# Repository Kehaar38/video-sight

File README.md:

# VIDEO SIGHT

VIDEO SIGHT is a compact digital sight prototype built around Seeed Studio XIAO ESP32-S3 Sense.

The project goal is a low-latency, approximately 1x-feeling video sight with camera input, LCD display, IMU-assisted attitude information, and a lightweight ballistic overlay for airsoft use.

## Current hardware direction

- Main MCU: Seeed Studio XIAO ESP32-S3 Sense
- Camera: XIAO ESP32-S3 Sense camera module
- Display: Waveshare 1.83 inch LCD Rev2 / ST7789P / 240x284
- IMU: BNO055 module
- UI sub-MCU: ATtiny1616
- Battery: protected 18650 cell
- microSD CS: GPIO21 on XIAO ESP32-S3 Sense
- Peripheral power switch: TPS22919, controlled by D6/GPIO43
- Reverse polarity protection: AO3401A P-MOSFET

## Repository layout

```text
docs/
  hardware/
    parts_and_pinout.md
    power/
    reviews/
hardware/
  kicad/
firmware/
  esp32s3/
  attiny1616/
```

## Status

Early hardware design. The current focus is the power path and first test PCB.

See:

- `docs/hardware/parts_and_pinout.md`
- `docs/hardware/power/power_bom.md`
- `docs/hardware/power/power_design_notes.md`
- `docs/hardware/reviews/2026-05-20_power_schematic_review.md`

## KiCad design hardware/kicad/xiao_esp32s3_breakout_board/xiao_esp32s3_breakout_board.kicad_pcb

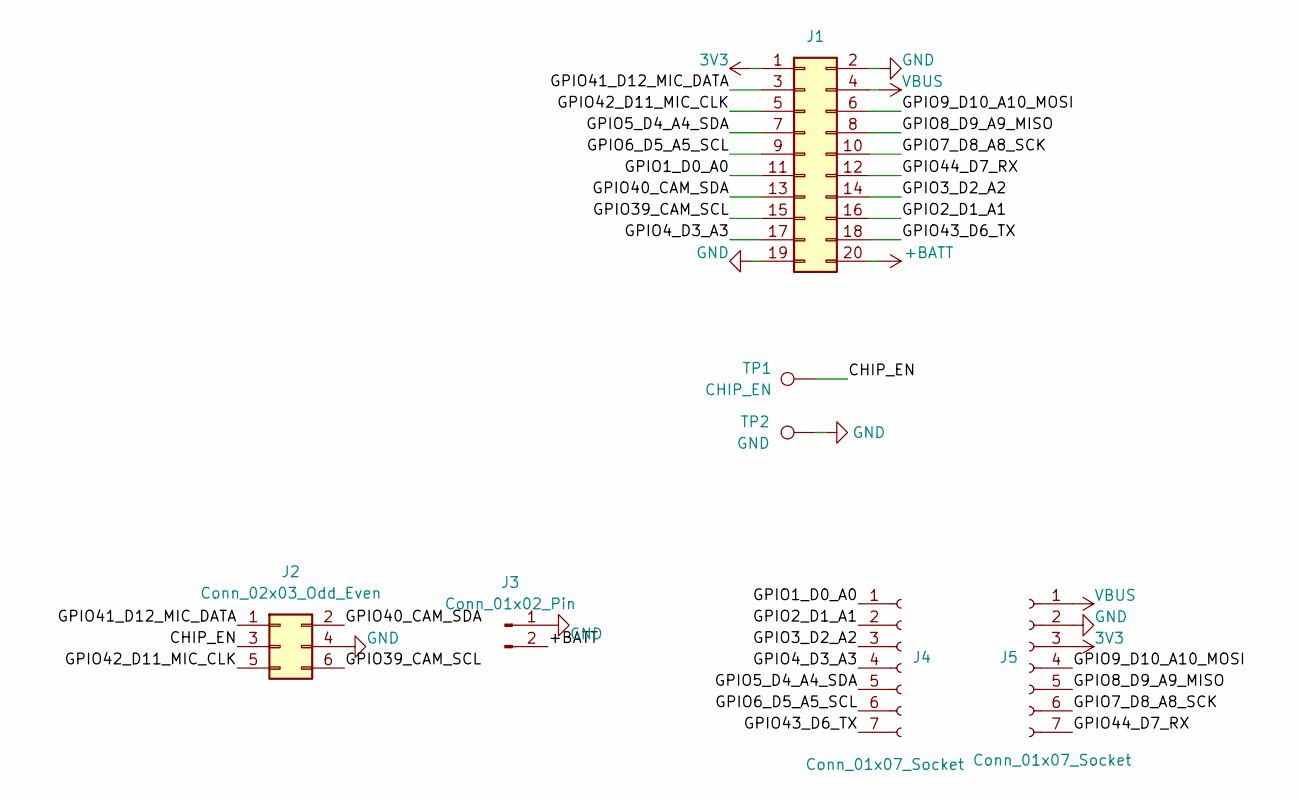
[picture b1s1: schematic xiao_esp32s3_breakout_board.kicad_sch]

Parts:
J1: XIAO_BREAKOUT_BOARD; IDC-Header_2x10_P2.54mm_Vertical
J2: Conn_02x03_Odd_Even; PinHeader_2x03_P2.54mm_Vertical
J3: Conn_01x02_Pin; PinHeader_1x02_P2.00mm_Vertical
J4, J5: Conn_01x07_Socket; PinSocket_1x07_P2.54mm_Vertical
TP1: CHIP_EN; TestPoint_THTPad_D1.5mm_Drill0.7mm
TP2: GND; TestPoint_THTPad_D1.5mm_Drill0.7mm

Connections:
3V3: J1.1, J5.3
+BATT: J1.20, J3.2
/CHIP_EN: J2.3, TP1.1
/GPIO1_D0_A0: J1.11, J4.1
/GPIO2_D1_A1: J1.16, J4.2
/GPIO3_D2_A2: J1.14, J4.3
/GPIO4_D3_A3: J1.17, J4.4
/GPIO5_D4_A4_SDA: J1.7, J4.5
/GPIO6_D5_A5_SCL: J1.9, J4.6
/GPIO7_D8_A8_SCK: J1.10, J5.6
/GPIO8_D9_A9_MISO: J1.8, J5.5
/GPIO9_D10_A10_MOSI: J1.6, J5.4
/GPIO39_CAM_SCL: J1.15, J2.6
/GPIO40_CAM_SDA: J1.13, J2.2
/GPIO41_D12_MIC_DATA: J1.3, J2.1
/GPIO42_D11_MIC_CLK: J1.5, J2.5
/GPIO43_D6_TX: J1.18, J4.7
/GPIO44_D7_RX: J1.12, J5.7
GND: J1.2, J1.19, J2.4, J3.1, J5.2, TP2.1
VBUS: J1.4, J5.1

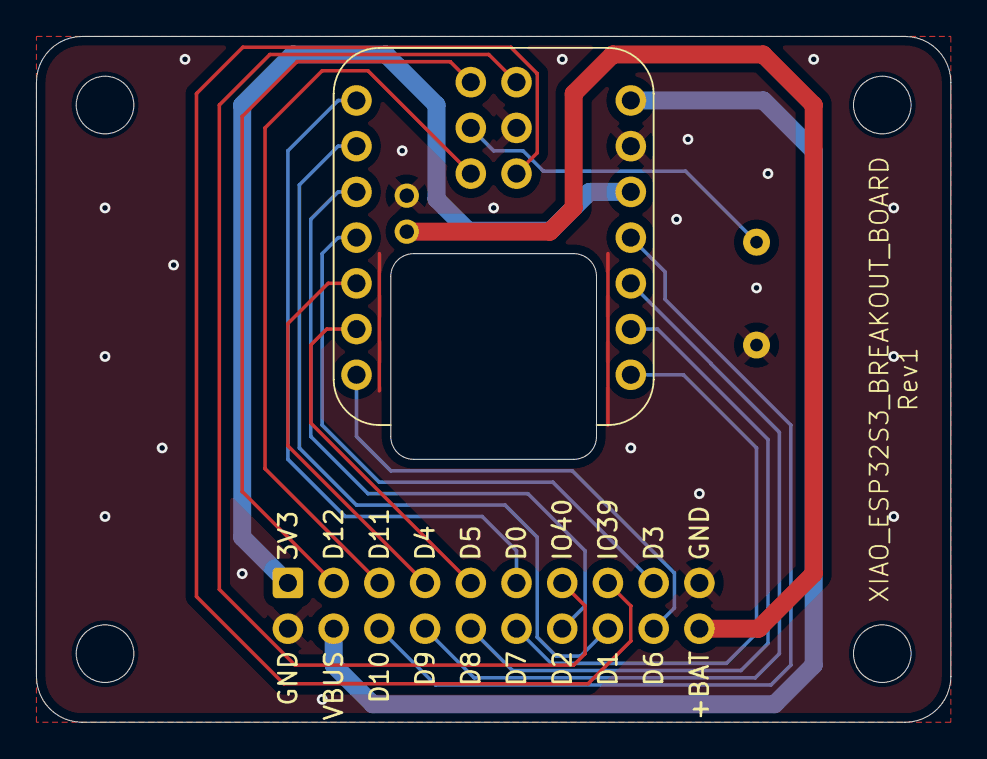
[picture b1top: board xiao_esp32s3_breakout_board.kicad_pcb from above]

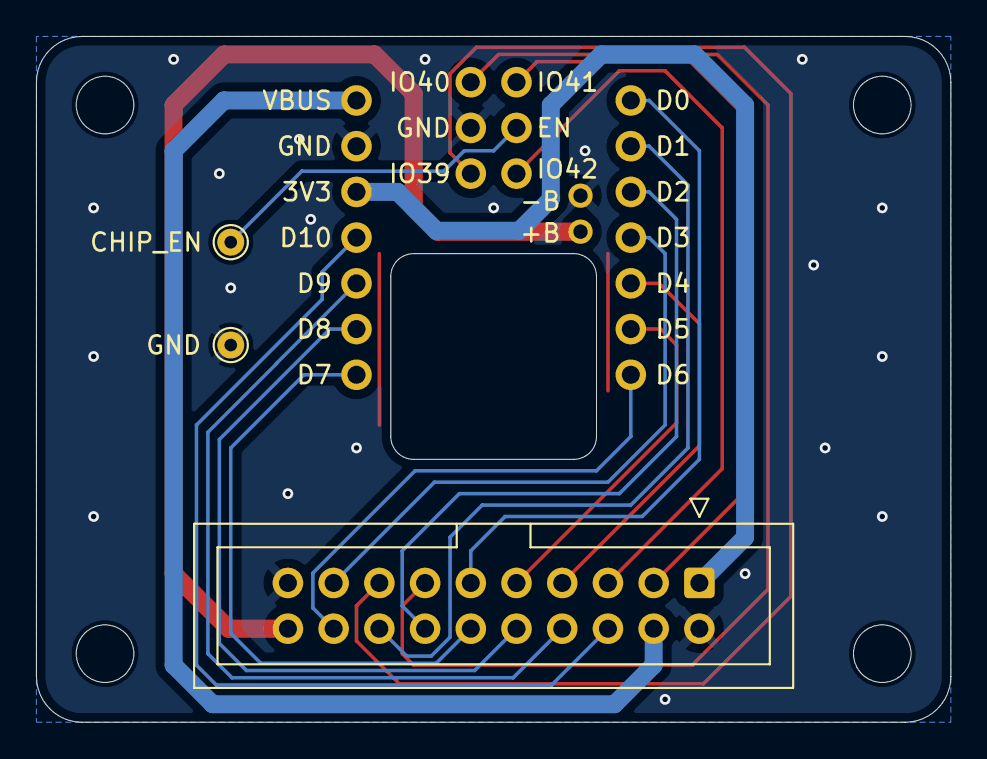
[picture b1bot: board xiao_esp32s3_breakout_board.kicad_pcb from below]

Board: 2 copper layers, 50.8 x 38.1 mm, 7 parts (3 on the bottom side), 20 nets.

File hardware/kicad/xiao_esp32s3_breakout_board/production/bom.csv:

Designator,Footprint,Quantity,Value,LCSC Part #
J1,IDC-Header_2x10_P2.54mm_Vertical,1,XIAO_BREAKOUT_BOARD,
J2,PinHeader_2x03_P2.54mm_Vertical,1,Conn_02x03_Odd_Even,
J3,PinHeader_1x02_P2.00mm_Vertical,1,Conn_01x02_Pin,
"J4, J5",PinSocket_1x07_P2.54mm_Vertical,2,Conn_01x07_Socket,
TP1,TestPoint_THTPad_D1.5mm_Drill0.7mm,1,CHIP_EN,
TP2,TestPoint_THTPad_D1.5mm_Drill0.7mm,1,GND,

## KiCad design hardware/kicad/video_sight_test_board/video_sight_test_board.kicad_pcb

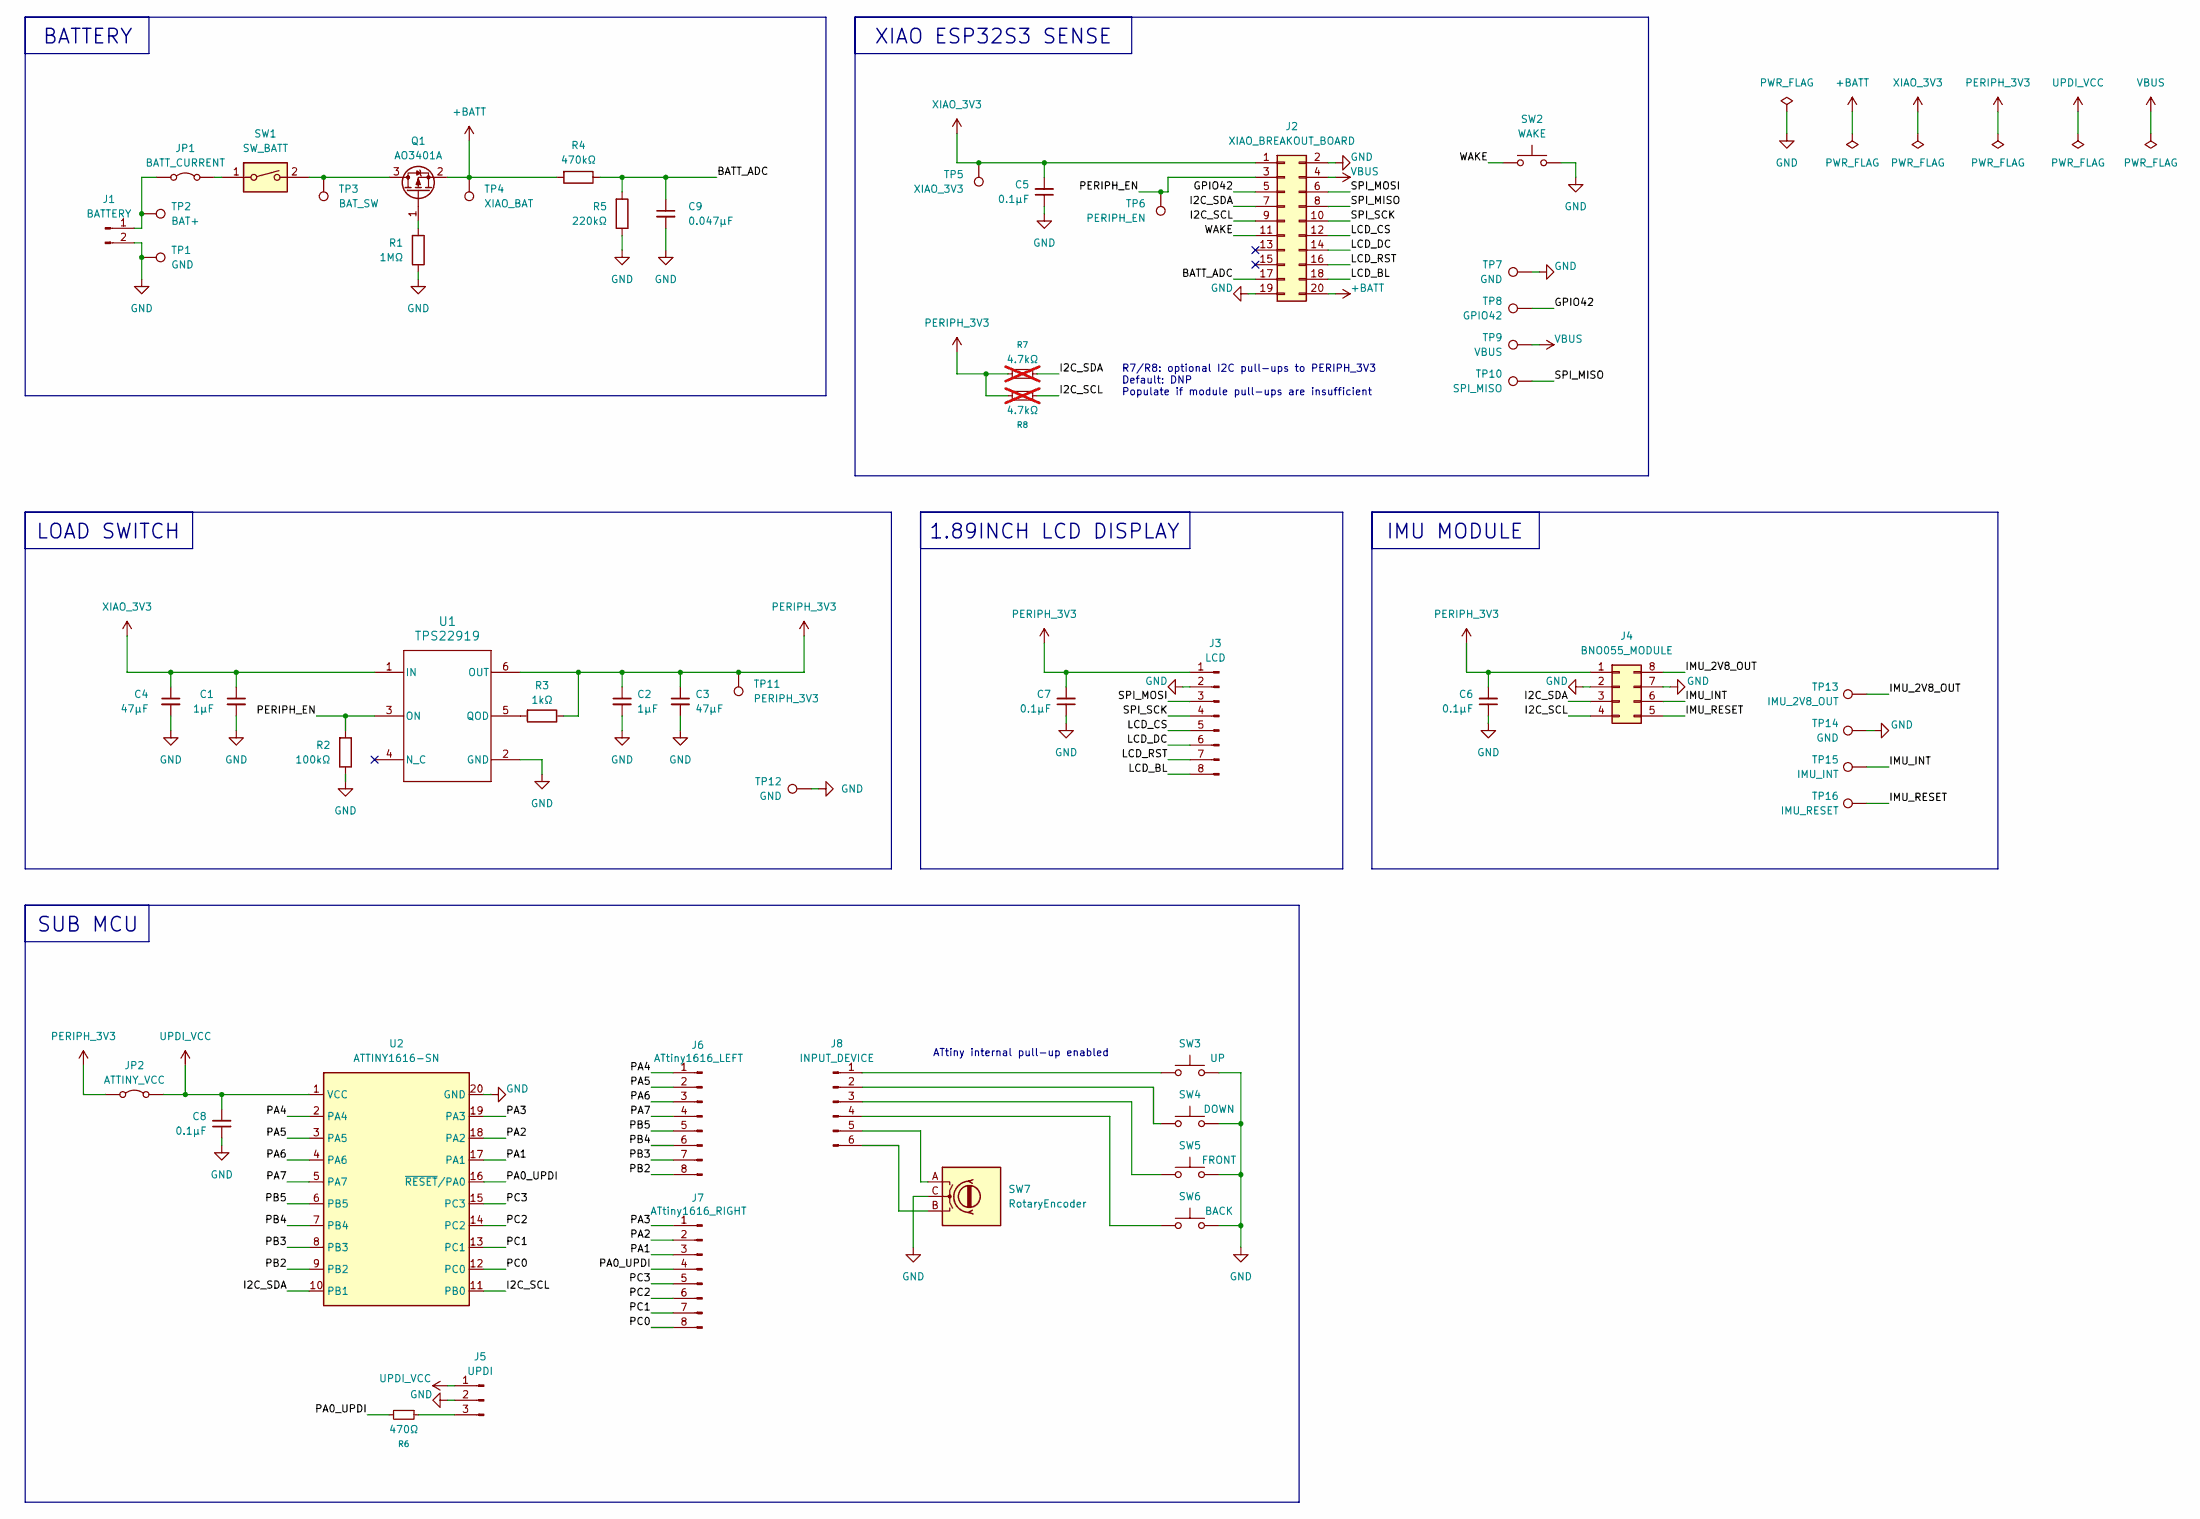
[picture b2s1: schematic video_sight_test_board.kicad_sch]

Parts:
C1, C2: 1μF; C_0805_2012Metric_Pad1.18x1.45mm_HandSolder
C3, C4: 47μF; CAP_FN_B_PAN
C5, C6, C7, C8: 0.1μF; C_0805_2012Metric_Pad1.18x1.45mm_HandSolder
C9: 0.047μF; C_0805_2012Metric_Pad1.18x1.45mm_HandSolder
J1: BATTERY; JST_XH_B2B-XH-A_1x02_P2.50mm_Vertical
J2: XIAO_BREAKOUT_BOARD; IDC-Header_2x10_P2.54mm_Vertical
J3: LCD; PinHeader_1x08_P2.54mm_Vertical
J4: BNO055_MODULE; DIP-8_W7.62mm_Socket
J5: UPDI; PinHeader_1x03_P2.54mm_Vertical
J6: ATtiny1616_LEFT; PinHeader_1x08_P2.54mm_Vertical
J7: ATtiny1616_RIGHT; PinHeader_1x08_P2.54mm_Vertical
J8: INPUT_DEVICE; PinHeader_1x06_P2.54mm_Vertical
JP1: BATT_CURRENT; PinHeader_1x02_P2.54mm_Vertical
JP2: ATTINY_VCC; PinHeader_1x02_P2.54mm_Vertical
Q1: AO3401A; SOT-23
R1: 1MΩ; R_0805_2012Metric_Pad1.20x1.40mm_HandSolder
R2: 100kΩ; R_0805_2012Metric_Pad1.20x1.40mm_HandSolder
R3: 1kΩ; R_0805_2012Metric_Pad1.20x1.40mm_HandSolder
R4: 470kΩ; R_0805_2012Metric_Pad1.20x1.40mm_HandSolder
R5: 220kΩ; R_0805_2012Metric_Pad1.20x1.40mm_HandSolder
R6: 470Ω; R_0805_2012Metric_Pad1.20x1.40mm_HandSolder
R7, R8: 4.7kΩ; R_0805_2012Metric_Pad1.20x1.40mm_HandSolder; not fitted
SW1: SW_BATT; SW_DIP_SPSTx01_Slide_9.78x4.72mm_W7.62mm_P2.54mm
SW2: WAKE; SW_PUSH_6mm
SW3: UP; SW_PUSH_6mm
SW4: DOWN; SW_PUSH_6mm
SW5: FRONT; SW_PUSH_6mm
SW6: BACK; SW_PUSH_6mm
SW7: RotaryEncoder; RotaryEncoder_Alps_EC12E_Vertical_H20mm
TP1, TP7, TP12, TP14: GND; TestPoint_THTPad_D1.5mm_Drill0.7mm
TP2: BAT+; TestPoint_THTPad_D1.5mm_Drill0.7mm
TP3: BAT_SW; TestPoint_THTPad_D1.5mm_Drill0.7mm
TP4: XIAO_BAT; TestPoint_THTPad_D1.5mm_Drill0.7mm
TP5: XIAO_3V3; TestPoint_THTPad_D1.5mm_Drill0.7mm
TP6: PERIPH_EN; TestPoint_THTPad_D1.5mm_Drill0.7mm
TP8: GPIO42; TestPoint_THTPad_D1.5mm_Drill0.7mm
TP9: VBUS; TestPoint_THTPad_D1.5mm_Drill0.7mm
TP10: SPI_MISO; TestPoint_THTPad_D1.5mm_Drill0.7mm
TP11: PERIPH_3V3; TestPoint_THTPad_D1.5mm_Drill0.7mm
TP13: IMU_2V8_OUT; TestPoint_THTPad_D1.5mm_Drill0.7mm
TP15: IMU_INT; TestPoint_THTPad_D1.5mm_Drill0.7mm
TP16: IMU_RESET; TestPoint_THTPad_D1.5mm_Drill0.7mm
U1: TPS22919; DCK0006A_L
U2: ATTINY1616-SN; SOIC-20W_7.5x12.8mm_P1.27mm

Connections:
+BATT: J2.20, Q1.2 (S), R4.2, TP4.1
/BATT_ADC: C9.1, J2.17, R4.1, R5.2
/GPIO42: J2.5, TP8.1
/I2C_SCL: J2.9, J4.4, R8.2, U2.11 (PB0)
/I2C_SDA: J2.7, J4.3, R7.2, U2.10 (PB1)
/IMU_2V8_OUT: J4.8, TP13.1
/IMU_INT: J4.6, TP15.1
/IMU_RESET: J4.5, TP16.1
/LCD_BL: J2.18, J3.8
/LCD_CS: J2.12, J3.5
/LCD_DC: J2.14, J3.6
/LCD_RST: J2.16, J3.7
/PA0_UPDI: J7.4, R6.2, U2.16 (~RESET/PA0)
/PA1: J7.3, U2.17 (PA1)
/PA2: J7.2, U2.18 (PA2)
/PA3: J7.1, U2.19 (PA3)
/PA4: J6.1, U2.2 (PA4)
/PA5: J6.2, U2.3 (PA5)
/PA6: J6.3, U2.4 (PA6)
/PA7: J6.4, U2.5 (PA7)
/PB2: J6.8, U2.9 (PB2)
/PB3: J6.7, U2.8 (PB3)
/PB4: J6.6, U2.7 (PB4)
/PB5: J6.5, U2.6 (PB5)
/PC0: J7.8, U2.12 (PC0)
/PC1: J7.7, U2.13 (PC1)
/PC2: J7.6, U2.14 (PC2)
/PC3: J7.5, U2.15 (PC3)
/PERIPH_EN: J2.3, R2.2, TP6.1, U1.3 (ON)
/SPI_MISO: J2.8, TP10.1
/SPI_MOSI: J2.6, J3.3
/SPI_SCK: J2.10, J3.4
/WAKE: J2.11, SW2.1
GND: C1.2, C2.2, C3.2, C4.2, C5.1, C6.1, C7.1, C8.1, C9.2, J1.2, J2.2, J2.19, J3.2, J4.2, J4.7, J5.2, R1.1, R2.1, R5.1, SW2.2, SW3.2, SW4.2, SW5.2, SW6.2, SW7.C, TP1.1, TP7.1, TP12.1, TP14.1, U1.2 (GND), U2.20 (GND)
unnamed: J1.1, JP1.1 (A), TP2.1
unnamed: J5.3, R6.1
unnamed: J8.1, SW3.1
unnamed: J8.2, SW4.1
unnamed: J8.3, SW5.1
unnamed: J8.4, SW6.1
unnamed: J8.5, SW7.A
unnamed: J8.6, SW7.B
unnamed: JP1.2 (B), SW1.1
unnamed: Q1.3 (D), SW1.2, TP3.1
unnamed: Q1.1 (G), R1.2
unnamed: R3.2, U1.5 (QOD)
PERIPH_3V3: C2.1, C3.1, C6.2, C7.2, J3.1, J4.1, JP2.1 (A), R3.1, R7.1, R8.1, TP11.1, U1.6 (OUT)
UPDI_VCC: C8.2, J5.1, JP2.2 (B), U2.1 (VCC)
VBUS: J2.4, TP9.1
XIAO_3V3: C1.1, C4.1, C5.2, J2.1, TP5.1, U1.1 (IN)

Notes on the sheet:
LOAD SWITCH
IMU MODULE
1.89INCH LCD DISPLAY
R7/R8: optional I2C pull-ups to PERIPH_3V3 Default: DNP Populate if module pull-ups are insufficient
XIAO ESP32S3 SENSE
SUB MCU
BATTERY
ATtiny internal pull-up enabled

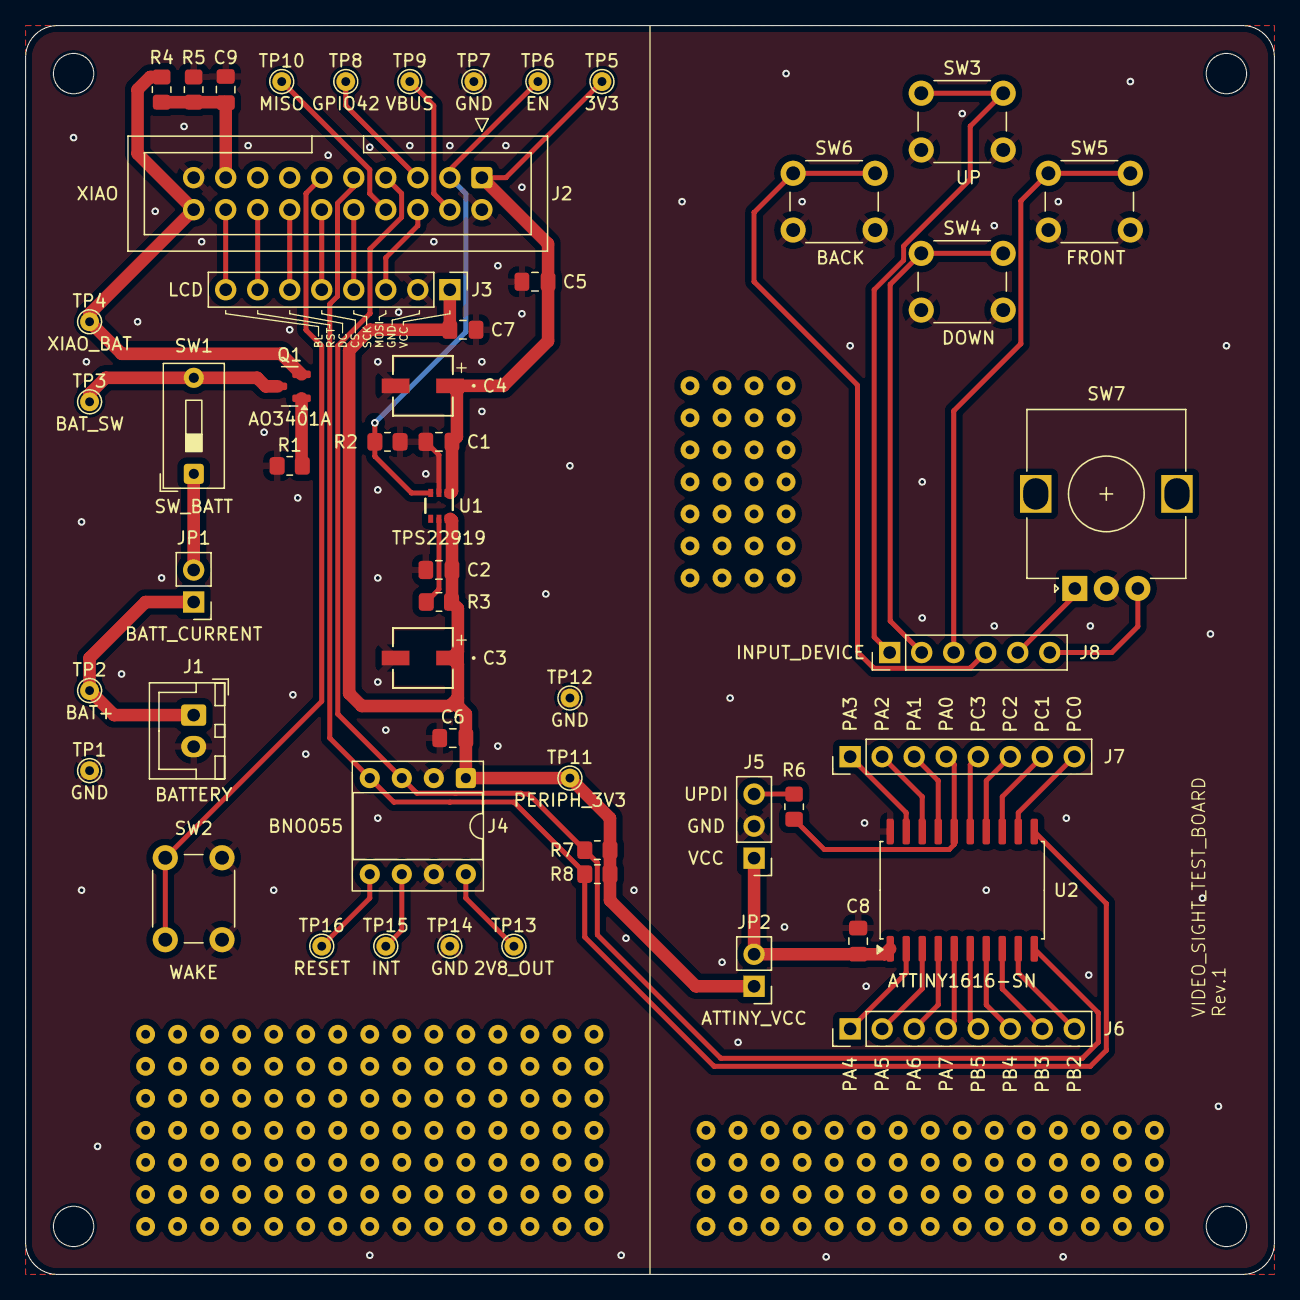
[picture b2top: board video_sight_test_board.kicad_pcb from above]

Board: 2 copper layers, 99.1 x 99.1 mm, 53 parts (0 on the bottom side), 50 nets.

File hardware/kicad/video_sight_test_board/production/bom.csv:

Designator,Footprint,Quantity,Value,LCSC Part #
"_193, _192, _191, _190, _189, _188, _187, _186, _185, _184, _183, _182, _181, _180, _179, _178, _177, _176, _175, _174, _173, _172, _171, _170, _169, _168, _167, _166, _165, _164, _163, _162, _161, _160, _159, _158, _157, _156, _155, _154, _153, _152, _151, _150, _149, _148, _147, _146, _145, _144, _143, _142, _141, _140, _139, _138, _137, _136, _135, _134, _133, _132, _131, _130, _129, _128, _127, _126, _125, _124, _123, _122, _121, _120, _119, _118, _117, _116, _115, _114, _113, _112, _111, _110, _109, _108, _107, _106, _105, _104, _103, _102, _101, _100, _99, _98, _97, _96, _95, _94, _93, _92, _91, _90, _89, _88, _87, _86, _85, _84, _83, _82, _81, _80, _79, _78, _77, _76, _75, _74, _73, _72, _71, _70, _69, _68, _67, _66, _65, _64, _63, _62, _61, _60, _59, _58, _57, _56, _55, _54, _53, _52, _51, _50, _49, _48, _47, _46, _45, _44, _43, _42, _41, _40, _39, _38, _37, _36, _35, _34, _33, _32, _31, _30, _29, _28, _27, _26, _25, _24, _23, _22, _21, _20, _19, _18, _17, _16, _15, _14, _13, _12, _11, _10, _9, _8, _7, _6, _5, _4, _3, _2, ",,193,,
"C1, C2",0805,2,1μF,
"C3, C4",CAP_FN_B_PAN,2,47μF,
"C5, C6, C7, C8",0805,4,0.1μF,
C9,0805,1,0.047μF,
J1,JST_XH_B2B-XH-A_1x02_P2.50mm_Vertical,1,BATTERY,
J2,IDC-Header_2x10_P2.54mm_Vertical,1,XIAO,
J3,PinHeader_1x08_P2.54mm_Vertical,1,LCD,
J4,DIP-8_W7.62mm_Socket,1,BNO055,
J5,PinHeader_1x03_P2.54mm_Vertical,1,UPDI,
J6,PinHeader_1x08_P2.54mm_Vertical,1,ATtiny1616_LEFT,
J7,PinHeader_1x08_P2.54mm_Vertical,1,ATtiny1616_RIGHT,
J8,PinHeader_1x06_P2.54mm_Vertical,1,INPUT_DEVICE,
JP1,PinHeader_1x02_P2.54mm_Vertical,1,BATT_CURRENT,
JP2,PinHeader_1x02_P2.54mm_Vertical,1,ATTINY_VCC,
Q1,SOT-23,1,AO3401A,
R1,0805,1,1MΩ,
R2,0805,1,100kΩ,
R3,0805,1,1kΩ,
R4,0805,1,470kΩ,
R5,0805,1,220kΩ,
R6,0805,1,470Ω,
"R7, R8",0805,2,4.7kΩ,
SW1,SW_DIP_SPSTx01_Slide_9.78x4.72mm_W7.62mm_P2.54mm,1,SW_BATT,
SW2,SW_PUSH_6mm,1,WAKE,
SW3,SW_PUSH_6mm,1,UP,
SW4,SW_PUSH_6mm,1,DOWN,
SW5,SW_PUSH_6mm,1,FRONT,
SW6,SW_PUSH_6mm,1,BACK,
SW7,RotaryEncoder_Alps_EC12E_Vertical_H20mm,1,RotaryEncoder,
"TP1, TP12, TP14, TP7",TestPoint_THTPad_D1.5mm_Drill0.7mm,4,GND,
TP10,TestPoint_THTPad_D1.5mm_Drill0.7mm,1,MISO,
TP11,TestPoint_THTPad_D1.5mm_Drill0.7mm,1,PERIPH_3V3,
TP13,TestPoint_THTPad_D1.5mm_Drill0.7mm,1,2V8_OUT,
TP15,TestPoint_THTPad_D1.5mm_Drill0.7mm,1,INT,
TP16,TestPoint_THTPad_D1.5mm_Drill0.7mm,1,RESET,
TP2,TestPoint_THTPad_D1.5mm_Drill0.7mm,1,BAT+,
TP3,TestPoint_THTPad_D1.5mm_Drill0.7mm,1,BAT_SW,
TP4,TestPoint_THTPad_D1.5mm_Drill0.7mm,1,XIAO_BAT,
TP5,TestPoint_THTPad_D1.5mm_Drill0.7mm,1,3V3,
TP6,TestPoint_THTPad_D1.5mm_Drill0.7mm,1,EN,
TP8,TestPoint_THTPad_D1.5mm_Drill0.7mm,1,GPIO42,
TP9,TestPoint_THTPad_D1.5mm_Drill0.7mm,1,VBUS,
U1,DCK0006A_L,1,TPS22919,
U2,SOIC-20W_7.5x12.8mm_P1.27mm,1,ATTINY1616-SN,

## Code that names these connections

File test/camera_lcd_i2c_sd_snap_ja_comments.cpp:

#include <Arduino.h>
#include <SPI.h>
#include <Wire.h>
#include <SD.h>
#include <FS.h>
#include <Adafruit_GFX.h>
#include <Adafruit_ST7789.h>
#include "esp_camera.h"

// ===== LCDのピン割り当て（docs/videosight_hardware_config_for_xiao_coding.mdより） =====
static constexpr int PIN_LCD_RST = 2;    // D1 / GPIO2
static constexpr int PIN_LCD_BL = 43;    // D6 / GPIO43
static constexpr int PIN_LCD_DC = 42;    // D11 / GPIO42
static constexpr int PIN_LCD_CS = 41;    // D12 / GPIO41
static constexpr int PIN_SPI_SCK = 7;    // D8 / GPIO7
static constexpr int PIN_SPI_MOSI = 9;   // D10 / GPIO9
static constexpr int PIN_SPI_MISO = 8;   // D9 / GPIO8
static constexpr int PIN_SD_CS = 21;     // オンボードSDのCS

// ===== LCDの表示サイズ =====
static constexpr int LCD_W = 240;
static constexpr int LCD_H = 280;
static constexpr int VIDEO_W = 240;
static constexpr int VIDEO_H = 240;
static constexpr int VIDEO_X = 0;
static constexpr int VIDEO_Y = (LCD_H - VIDEO_H) / 2;  // 20
static constexpr int LCD_ROTATION = 2;                  // 0..3（2 = 180度回転）

SPIClass lcdSpi(FSPI);
Adafruit_ST7789 tft(&lcdSpi, PIN_LCD_CS, PIN_LCD_DC, PIN_LCD_RST);

// ===== XIAO ESP32S3 Sense カメラのピンマップ（OV2640） =====
// カメラモジュールのリビジョン違いで初期化失敗する場合は、
// 以下のピン定義を実機のピンマップに合わせて修正する。
static constexpr int CAM_PWDN = -1;
static constexpr int CAM_RESET = -1;
static constexpr int CAM_XCLK = 10;
static constexpr int CAM_SIOD = 40;
static constexpr int CAM_SIOC = 39;

static constexpr int CAM_Y9 = 48;
static constexpr int CAM_Y8 = 11;
static constexpr int CAM_Y7 = 12;
static constexpr int CAM_Y6 = 14;
static constexpr int CAM_Y5 = 16;
static constexpr int CAM_Y4 = 18;
static constexpr int CAM_Y3 = 17;
static constexpr int CAM_Y2 = 15;
static constexpr int CAM_VSYNC = 38;
static constexpr int CAM_HREF = 47;
static constexpr int CAM_PCLK = 13;
static constexpr int CAM_HMIRROR = 1;  // 0: 通常, 1: 左右反転
static constexpr int CAM_VFLIP = 0;    // 0: 通常, 1: 上下反転

// ===== I2C InputDevice =====
static constexpr int PIN_I2C_SDA = 5;                 // D4 / GPIO5
static constexpr int PIN_I2C_SCL = 6;                 // D5 / GPIO6
static constexpr uint8_t INPUT_I2C_ADDR = 0x12;
static constexpr uint8_t INPUT_BIT_FRONT = 2;         // 旧RIGHTボタン相当ビット

static bool g_frontPressed = false;
static bool g_prevFrontPressed = false;
static bool g_sdReady = false;

static void writeLe16(File &f, uint16_t v) {
  f.write((uint8_t)(v & 0xFF));
  f.write((uint8_t)((v >> 8) & 0xFF));
}

static void writeLe32(File &f, uint32_t v) {
  f.write((uint8_t)(v & 0xFF));
  f.write((uint8_t)((v >> 8) & 0xFF));
  f.write((uint8_t)((v >> 16) & 0xFF));
  f.write((uint8_t)((v >> 24) & 0xFF));
}

static bool saveRgb565AsBmp(const uint8_t *rgb565, int w, int h) {
  if (!g_sdReady) {
    return false;
  }

  char path[32];
  int idx = 1;
  do {
    snprintf(path, sizeof(path), "/snap_%04d.bmp", idx++);
  } while (SD.exists(path) && idx < 10000);

  File file = SD.open(path, FILE_WRITE);
  if (!file) {
    Serial.println("Failed to open snapshot file");
    return false;
  }

  const uint32_t pixelBytes = (uint32_t)w * (uint32_t)h * 2U;
  const uint32_t headerBytes = 14U + 40U + 12U;  // BMPヘッダ + DIBヘッダ + RGB565マスク
  const uint32_t fileSize = headerBytes + pixelBytes;

  // BMPファイルヘッダ（14バイト）
  file.write('B');
  file.write('M');
  writeLe32(file, fileSize);
  writeLe16(file, 0);
  writeLe16(file, 0);
  writeLe32(file, headerBytes);

  // BITMAPINFOHEADER（40バイト）
  writeLe32(file, 40);               // biSize
  writeLe32(file, (uint32_t)w);      // biWidth
  writeLe32(file, (uint32_t)(-h));   // biHeight（負値=top-down）
  writeLe16(file, 1);                // biPlanes
  writeLe16(file, 16);               // biBitCount
  writeLe32(file, 3);                // biCompression = BI_BITFIELDS
  writeLe32(file, pixelBytes);       // biSizeImage
  writeLe32(file, 2835);             // biXPelsPerMeter
  writeLe32(file, 2835);             // biYPelsPerMeter
  writeLe32(file, 0);                // biClrUsed
  writeLe32(file, 0);                // biClrImportant

  // RGB565マスク（12バイト）
  writeLe32(file, 0xF800);           // Rマスク
  writeLe32(file, 0x07E0);           // Gマスク
  writeLe32(file, 0x001F);           // Bマスク

  // 画素データ本体
  const size_t written = file.write(rgb565, pixelBytes);
  file.close();
  if (written != pixelBytes) {
    Serial.println("Snapshot write size mismatch");
    return false;
  }

  Serial.printf("SNAP saved: %s (%lu bytes)\n", path, (unsigned long)fileSize);
  return true;
}

static void updateInputDeviceState() {
  g_prevFrontPressed = g_frontPressed;

  const int req = Wire.requestFrom((int)INPUT_I2C_ADDR, 2);
  if (req < 2) {
    return;
  }

  const int8_t encDelta = (int8_t)Wire.read();
  (void)encDelta;  // このサンプルでは未使用

  const uint8_t b1 = (uint8_t)Wire.read();
  const uint8_t buttons = (uint8_t)(b1 & 0x1F);  // 下位5bit = ボタン状態
  g_frontPressed = (buttons & (1U << INPUT_BIT_FRONT)) != 0;
}

static bool initCamera() {
  camera_config_t config = {};
  config.ledc_channel = LEDC_CHANNEL_0;
  config.ledc_timer = LEDC_TIMER_0;
  config.pin_d0 = CAM_Y2;
  config.pin_d1 = CAM_Y3;
  config.pin_d2 = CAM_Y4;
  config.pin_d3 = CAM_Y5;
  config.pin_d4 = CAM_Y6;
  config.pin_d5 = CAM_Y7;
  config.pin_d6 = CAM_Y8;
  config.pin_d7 = CAM_Y9;
  config.pin_xclk = CAM_XCLK;
  config.pin_pclk = CAM_PCLK;
  config.pin_vsync = CAM_VSYNC;
  config.pin_href = CAM_HREF;
  config.pin_sccb_sda = CAM_SIOD;
  config.pin_sccb_scl = CAM_SIOC;
  config.pin_pwdn = CAM_PWDN;
  config.pin_reset = CAM_RESET;
  config.xclk_freq_hz = 20000000;
  config.frame_size = FRAMESIZE_240X240;
  config.pixel_format = PIXFORMAT_RGB565;
  config.grab_mode = CAMERA_GRAB_LATEST;
  config.fb_location = CAMERA_FB_IN_PSRAM;
  config.jpeg_quality = 12;
  config.fb_count = 2;

  const esp_err_t err = esp_camera_init(&config);
  if (err != ESP_OK) {
    Serial.printf("esp_camera_init failed: 0x%x\n", err);
    return false;
  }

  sensor_t *sensor = esp_camera_sensor_get();
  if (sensor != nullptr) {
    sensor->set_vflip(sensor, CAM_VFLIP);
    sensor->set_hmirror(sensor, CAM_HMIRROR);
    sensor->set_brightness(sensor, 0);
    sensor->set_saturation(sensor, 0);
  }
  return true;
}

static void initLcd() {
  pinMode(PIN_LCD_BL, OUTPUT);
  digitalWrite(PIN_LCD_BL, LOW);

  lcdSpi.begin(PIN_SPI_SCK, PIN_SPI_MISO, PIN_SPI_MOSI, PIN_LCD_CS);
  tft.init(240, 280);
  tft.setRotation(LCD_ROTATION);
  tft.fillScreen(ST77XX_BLACK);

  digitalWrite(PIN_LCD_BL, HIGH);
}

static bool initSdCard() {
  if (!SD.begin(PIN_SD_CS, lcdSpi)) {
    Serial.println("SD.begin failed");
    return false;
  }
  uint64_t cardSizeMb = SD.cardSize() / (1024ULL * 1024ULL);
  Serial.printf("SD ready: %llu MB\n", cardSizeMb);
  return true;
}

static void drawStatus(const char *msg, uint16_t color) {
  tft.fillScreen(ST77XX_BLACK);
  tft.setTextColor(color);
  tft.setTextSize(2);
  tft.setCursor(10, 130);
  tft.print(msg);
}

void setup() {
  Serial.begin(115200);
  delay(300);

  initLcd();
  drawStatus("Init camera...", ST77XX_YELLOW);
  Wire.begin(PIN_I2C_SDA, PIN_I2C_SCL, 100000);

  if (!initCamera()) {
    drawStatus("Camera init NG", ST77XX_RED);
    return;
  }

  g_sdReady = initSdCard();
  if (!g_sdReady) {
    Serial.println("SNAP disabled: SD not available");
  }

  drawStatus("Camera init OK", ST77XX_GREEN);
  delay(500);
  tft.fillScreen(ST77XX_BLACK);
}

void loop() {
  camera_fb_t *fb = esp_camera_fb_get();
  if (fb == nullptr) {
    Serial.println("esp_camera_fb_get failed");
    return;
  }

  if (fb->format == PIXFORMAT_RGB565 && fb->width == VIDEO_W && fb->height == VIDEO_H) {
    // XIAO ESP32S3 SenseのフレームバッファはRGB565のバイト順が
    // Adafruit_ST7789の期待順と異なることがあるため、描画前にスワップする。
    for (size_t i = 0; i + 1 < fb->len; i += 2) {
      const uint8_t hi = fb->buf[i];
      fb->buf[i] = fb->buf[i + 1];
      fb->buf[i + 1] = hi;
    }
    tft.drawRGBBitmap(VIDEO_X, VIDEO_Y, reinterpret_cast<uint16_t *>(fb->buf), VIDEO_W, VIDEO_H);

    updateInputDeviceState();
    const bool frontRisingEdge = (!g_prevFrontPressed && g_frontPressed);
    if (frontRisingEdge) {
      const bool ok = saveRgb565AsBmp(fb->buf, VIDEO_W, VIDEO_H);
      if (!ok) {
        Serial.println("SNAP failed");
      }
    }
  } else {
    static uint32_t lastWarn = 0;
    const uint32_t now = millis();
    if (now - lastWarn > 1000) {
      lastWarn = now;
      Serial.printf("Unexpected frame format/size: fmt=%d w=%d h=%d\n",
                    static_cast<int>(fb->format), fb->width, fb->height);
    }
  }

  esp_camera_fb_return(fb);
}

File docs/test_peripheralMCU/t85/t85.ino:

// EventNode1 (ATtiny85, 8MHz, 3.3V)
// EVENT省略版
//
// PB0: UART TX -> PeripheralMCU
// PB1: 未使用（前回は EVENT出力）
// PB2: タクトスイッチ入力
// PB3: 未使用（前回は UART RX）
// PB4: デバッグLED（任意）
//
// 動作:
// - スイッチ変化を検知
// - イベント発生時にUARTフレームを即送信
//
// 前回片側UART版との差分:
// - EVENT線を使わない
// - setEventLine() 削除
// - EVENT_HOLD_MS 削除
// - PB1 は未使用

#include <Arduino.h>
#include <SoftwareSerial.h>

// ------------------------------
// ピン定義
// ------------------------------
static const uint8_t PIN_UART_TX   = PB0;
static const uint8_t PIN_UNUSED_1  = PB1;  // 前回は EVENT
static const uint8_t PIN_SWITCH    = PB2;
static const uint8_t PIN_UNUSED_2  = PB3;  // 前回は UART RX
static const uint8_t PIN_LED       = PB4;

// ------------------------------
// 固定値
// ------------------------------
static const uint32_t UART_BAUD = 9600;

static const uint8_t FRAME_HEADER  = 0xA5;
static const uint8_t FRAME_VERSION = 0x01;

// EventNode1 の種別値
static const uint8_t NODE_TYPE_VALUE = 0x11;

// イベント種別
static const uint8_t EVENT_TYPE_SWITCH_PRESSED  = 0x02;
static const uint8_t EVENT_TYPE_SWITCH_RELEASED = 0x03;

// デバウンス関連
static const uint16_t DEBOUNCE_MS        = 40;
static const uint16_t RETRIGGER_GUARD_MS = 60;

// SoftwareSerial
// RX は未使用だが、コンストラクタ都合でダミー指定
SoftwareSerial nodeSerial(PIN_UNUSED_2, PIN_UART_TX);

// ------------------------------
// イベント送信
// ------------------------------
uint8_t g_eventIdCounter = 0;

// フレーム送信
void sendEventFrame(uint8_t eventType, uint8_t meta0, uint8_t meta1, uint8_t flags) {
  uint16_t ts = (uint16_t)millis();

  uint8_t buf[11];
  buf[0]  = FRAME_HEADER;
  buf[1]  = FRAME_VERSION;
  buf[2]  = g_eventIdCounter++;
  buf[3]  = eventType;
  buf[4]  = NODE_TYPE_VALUE;
  buf[5]  = (uint8_t)(ts & 0xFF);
  buf[6]  = (uint8_t)((ts >> 8) & 0xFF);
  buf[7]  = meta0;
  buf[8]  = meta1;
  buf[9]  = flags;

  uint8_t checksum = 0;
  for (uint8_t i = 0; i < 10; ++i) {
    checksum ^= buf[i];
  }
  buf[10] = checksum;

  for (uint8_t i = 0; i < sizeof(buf); ++i) {
    nodeSerial.write(buf[i]);
  }
  nodeSerial.flush();
}

void setup() {
  pinMode(PIN_SWITCH, INPUT_PULLUP);

  pinMode(PIN_LED, OUTPUT);
  digitalWrite(PIN_LED, LOW);

  nodeSerial.begin(UART_BAUD);
}

void loop() {
  static bool debouncedState = true;    // true=離されている
  static bool lastRawState   = true;
  static uint32_t lastChangeAt = 0;
  static uint32_t lastAcceptedEventAt = 0;

  bool raw = digitalRead(PIN_SWITCH);

  if (raw != lastRawState) {
    lastRawState = raw;
    lastChangeAt = millis();
  }

  if ((millis() - lastChangeAt) >= DEBOUNCE_MS && raw != debouncedState) {
    if ((millis() - lastAcceptedEventAt) >= RETRIGGER_GUARD_MS) {
      debouncedState = raw;
      lastAcceptedEventAt = millis();

      digitalWrite(PIN_LED, !digitalRead(PIN_LED));

      if (!debouncedState) {
        // 押下
        sendEventFrame(EVENT_TYPE_SWITCH_PRESSED, 0x01, 0x00, 0x00);
      } else {
        // 解放
        sendEventFrame(EVENT_TYPE_SWITCH_RELEASED, 0x00, 0x00, 0x00);
      }
    } else {
      debouncedState = raw;
    }
  }
}

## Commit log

2026-03-04 Add initial project structure with configuration files and example code
2026-03-04 日本語のコメントに翻訳: platformio.ini と README ファイルの内容を日本語に更新
2026-03-08 VideoSightのハード構成とメニュー画面仕様をChatGPTログから抽出し、文書化
2026-03-08 VIDEO SIGHT GUID MENUの初回作成とボタンシンボル、オーバーレイ、画面遷移図の詳細を追加
2026-03-09 platformio.iniにモニタースピードとライブラリ依存関係を追加
2026-03-09 XIAO ESP32S3 Sense用のカメラとLCDの初期化コードを追加
2026-03-09 XIAO ESP32S3 Sense用のカメラ、LCD、I2C、SDカードの初期化とスナップショット機能を追加
2026-03-09 メインモードガイドをLCDに描画する機能を追加し、CP437記号を有効化
2026-03-11 Rgb565Overlayクラスを追加し、drawMainModeGuide関数をAdafruit_GFXを使用するように変更
2026-03-11 ATmega328Pファームウェアの初期化コードとプロトコルドキュメントを追加
2026-03-12 PeripheralMCUとEventNode1のテストコードを追加
2026-03-15 Add EventNode and VideoSight Input/EventHub specifications
    - Implement EventNode functionality for ATtiny85 with UART communication.
    - Create VideoSight Input/EventHub specification document detailing system architecture, roles, and communication protocols.
    - Develop Virtual VideoSight for XIAO ESP32 to handle I2C communication and display events.
2026-03-16 Refactor EventNode1 for ATtiny85 and ATmega328P; implement new VideoSight ⇔ PeripheralMCU communication protocol v1.0
    - Updated ATtiny85 code to remove bidirectional UART support and simplify event handling.
    - Introduced a new communication protocol document detailing I2C and EVENT line interactions between VideoSight and PeripheralMCU.
    - Added ATmega328P implementation for bidirectional UART communication with event queue management.
    - Enhanced event frame structure and processing logic for better clarity and performance.
    - Established a robust error handling and timing requirement section in the protocol documentation.
2026-03-16 LCDリセットピンの割り当てを修正
2026-03-16 LCDリセットピンのコメントを修正
2026-03-17 Refactor ATtiny85 code for single UART usage
2026-03-17 Refactor comments and update serviceNode1 logic
    Updated comments and pin definitions for clarity and to reflect changes from the previous version. Adjusted serviceNode1 function to only monitor UART buffer due to the absence of the EVENT line.
2026-05-21 Initial VIDEO SIGHT design documentation
2026-05-21 KiCADファイル新規追加
2026-05-21 issue #1 #3 #4 対応
2026-05-21 XIAO ネットラベル追加 電流測定ジャンパー追加 PERIPH/XIAOバルクコンデンサ追加
2026-05-21 KiCAD一時ファイル除外
2026-05-21 回路図スクリーンショット
2026-05-21 Add XIAO breakout board notes
2026-05-23 ディレクトリ名修正
2026-05-23 回路図更新
2026-05-23 Review updated test-board schematic
2026-05-23 XIAO ESP32S3 ブレイクアウトボード作成
2026-05-23 テストボード回路図修正 SPI_MOSI 体裁
2026-05-23 Review XIAO breakout schematic fixes
2026-05-23 IMU未使用ピン TP追加 他
2026-05-23 Add ATtiny1616 UPDI programming power notes
2026-05-23 UPDI書き込み端子追加 内部プルアップ注記追加
2026-05-23 Review ATtiny UPDI and IMU schematic updates
2026-05-23 Clarify IMU update added test points
2026-05-23 テストボード回路図修正 I2Cプルアップ追加 C8位置修正
2026-05-23 Review C8 and I2C pull-up updates
2026-05-23 リファレンス修正
2026-05-23 I2Cプルアップ注記追加
2026-05-23 Add final test-board schematic review
2026-05-23 Add test point footprint notes
2026-05-24 フットプリント選定 微修正
2026-05-24 Review footprint selection
2026-05-24 Document footprint and cable follow-up decisions
2026-05-24 WAKEスイッチ追加 TP10修正
2026-05-24 Update test-board BOM after ERC fixes
2026-05-24 PCB途中
2026-05-25 PCBざっくり置いた
2026-05-26 テストボードPCBだいたい完成
2026-05-26 テストボードPCBレビューを追加
2026-05-26 シルク追加
2026-05-26 PCBシルク追加確認を追記
2026-05-27 ブレイクアウトボード作成中
2026-05-28 初期弾道予測モデルを文書化
2026-05-29 プロットシミュレーション作成
2026-06-01 これで注文した
2026-06-10 PlatformIO初期化
2026-06-11 SD CS確認用テストを追加
2026-06-11 SD CSテストをexamplesへ退避
2026-06-11 LCD解像度確認テストを追加
2026-06-11 解像度テスト
2026-06-12 LCD表示確認結果を反映
2026-06-12 カメラFOV撮影テストを追加
2026-06-12 カメラ表示の色と上下反転を補正
2026-06-12 カメラ撮影テストのSD初期化を改善
2026-06-13 LovyanGFXの共有SPI設定を調整
2026-06-14 BMP保存時のRGB565色変換を修正
2026-06-14 カメラFOV実測値を1倍クロップへ反映
2026-06-14 1倍表示の想定視距離を150mmへ変更
2026-06-14 QXGA等倍クロップを試行
2026-06-14 QXGA失敗を受けUXGAクロップへ戻す
2026-06-14 UXGA失敗を受けXGAクロップへ下げる
2026-06-15 FOV確認用スケッチをexampleへ退避
2026-06-15 OV3660センサー側ROIクロップを試行
2026-06-15 ROI試行を240x240へ切り分け
2026-06-15 240x240 ROI実機確認結果を記録
2026-06-15 320x320 ROI中央表示を試行
2026-06-15 320x320 ROI失敗を受けCIF ROIを試行
2026-06-15 CIF ROI表示経路を軽量化
